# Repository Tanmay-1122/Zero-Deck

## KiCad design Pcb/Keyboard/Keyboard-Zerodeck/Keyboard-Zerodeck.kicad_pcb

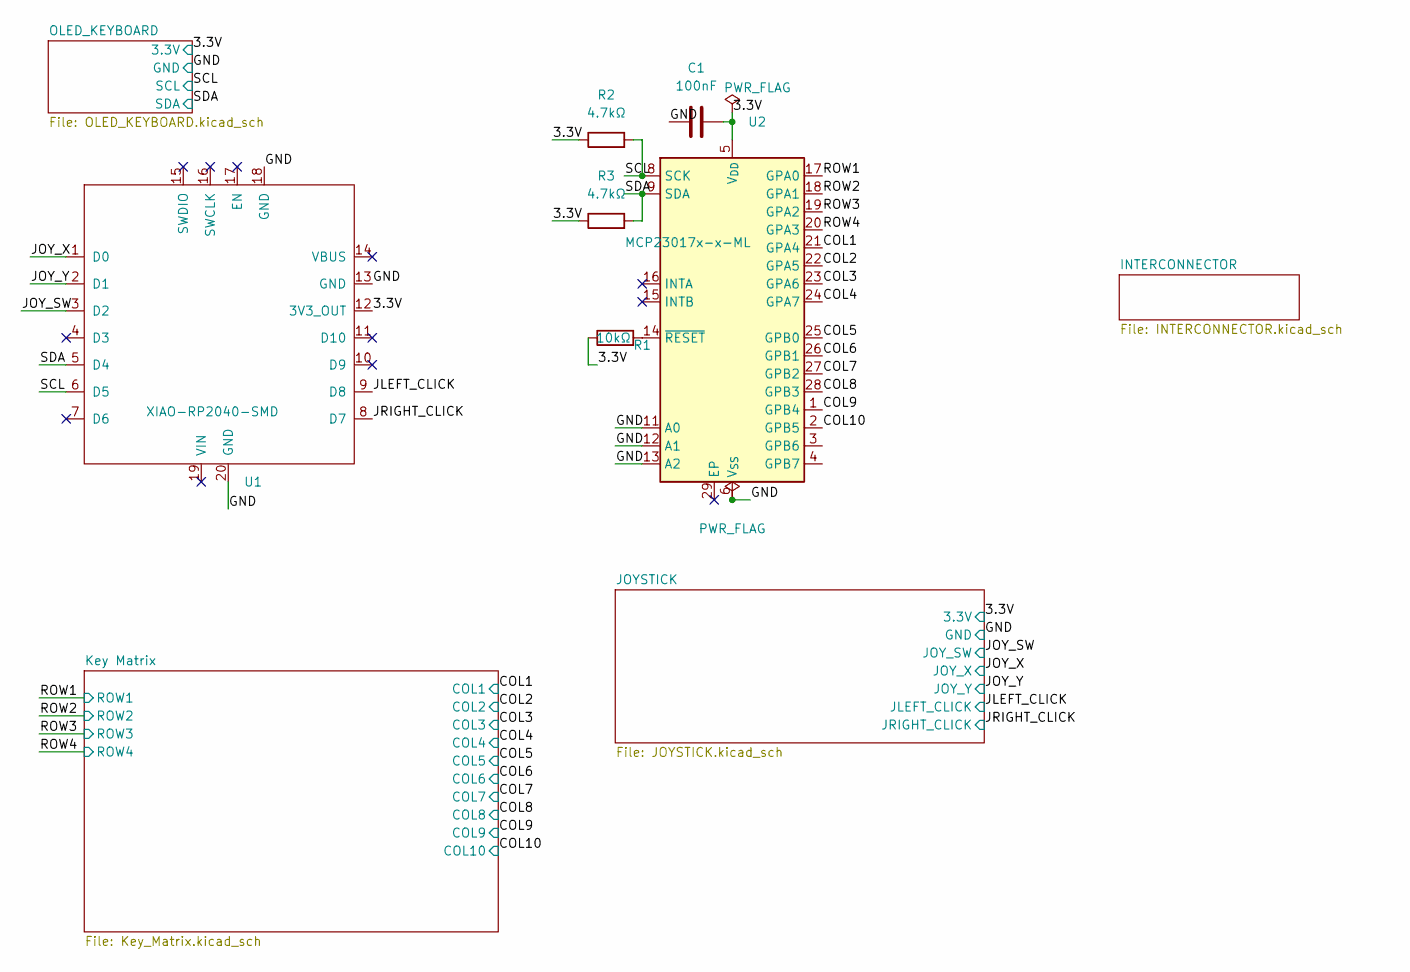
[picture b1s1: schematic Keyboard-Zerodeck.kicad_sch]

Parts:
C1: 100nF; C_0805_2012Metric
R1: 10kΩ; R_0805_2012Metric
R2, R3: 4.7kΩ; R_0805_2012Metric
U1: XIAO-RP2040-SMD
U2: MCP23017x-x-ML; QFN-28-1EP_6x6mm_P0.65mm_EP4.25x4.25mm

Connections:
/3.3V: C1.2, R1.1, R2.1, R3.1, U1.12 (3V3_OUT), U2.5 (V_{DD}); also elsewhere on the board
/COL1: U2.21 (GPA4); also elsewhere on the board
/COL2: U2.22 (GPA5); also elsewhere on the board
/COL3: U2.23 (GPA6); also elsewhere on the board
/COL4: U2.24 (GPA7); also elsewhere on the board
/COL5: U2.25 (GPB0); also elsewhere on the board
/COL6: U2.26 (GPB1); also elsewhere on the board
/COL7: U2.27 (GPB2); also elsewhere on the board
/COL8: U2.28 (GPB3); also elsewhere on the board
/COL9: U2.1 (GPB4); also elsewhere on the board
/COL10: U2.2 (GPB5); also elsewhere on the board
/GND: C1.1, U1.13 (GND), U1.18 (GND), U1.20 (GND), U2.6 (V_{SS}), U2.11 (A0), U2.12 (A1), U2.13 (A2); also elsewhere on the board
/JLEFT_CLICK: U2.3 (GPB6); also elsewhere on the board
/JOY_SW: U1.3 (D2); also elsewhere on the board
/JOY_X: U1.1 (D0); also elsewhere on the board
/JOY_Y: U1.2 (D1); also elsewhere on the board
/JRIGHT_CLICK: U2.4 (GPB7); also elsewhere on the board
/ROW1: U2.17 (GPA0); also elsewhere on the board
/ROW2: U2.18 (GPA1); also elsewhere on the board
/ROW3: U2.19 (GPA2); also elsewhere on the board
/ROW4: U2.20 (GPA3); also elsewhere on the board
/SCL: R2.2, U1.6 (D5), U2.8 (SCK)
/sda: R3.2, U1.5 (D4), U2.9 (SDA)
unnamed: R1.2, U2.14 (~RESET)

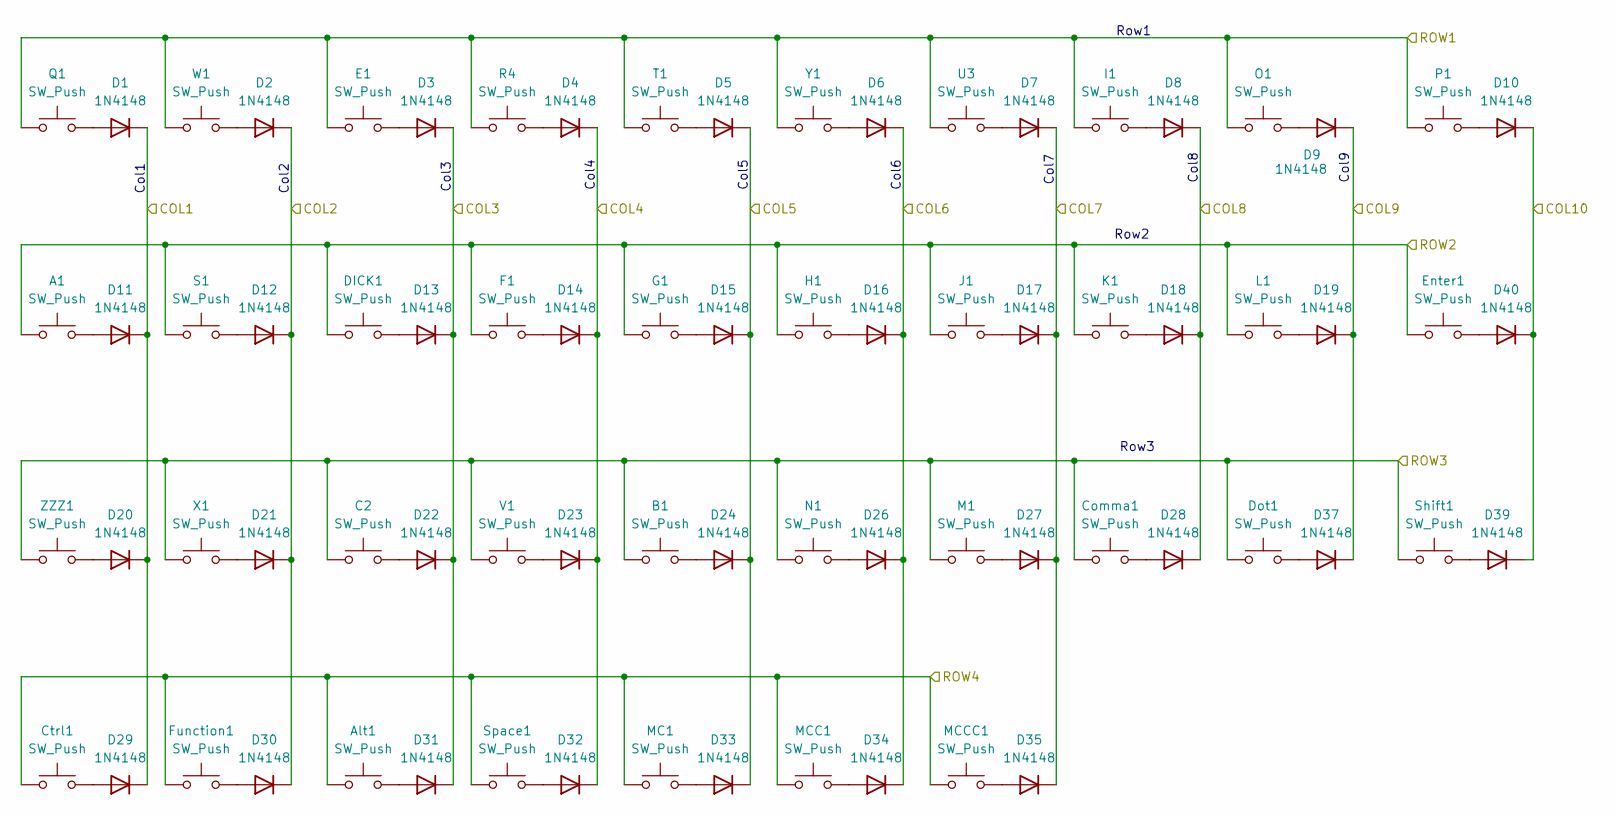
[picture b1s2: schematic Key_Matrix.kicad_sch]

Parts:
A1: SW_Push; Kailh_socket_PG1350
Alt1: SW_Push; Kailh_socket_PG1350
B1: SW_Push; Kailh_socket_PG1350
C2: SW_Push; Kailh_socket_PG1350
Comma1: SW_Push; Kailh_socket_PG1350
Ctrl1: SW_Push; Kailh_socket_PG1350
D1, D2, D3, D4, D5, D6, D7, D8, D9, D10, D11, D12, D13, D14, D15, D16, D17, D18, D19, D20, D21, D22, D23, D24, D26, D27, D28, D29, D30, D31, D32, D33, D34, D35, D37, D39, D40: 1N4148; D_SOD-123
DICK1: SW_Push; Kailh_socket_PG1350
Dot1: SW_Push; Kailh_socket_PG1350
E1: SW_Push; Kailh_socket_PG1350
Enter1: SW_Push; Kailh_socket_PG1350
F1: SW_Push; Kailh_socket_PG1350
Function1: SW_Push; Kailh_socket_PG1350
G1: SW_Push; Kailh_socket_PG1350
H1: SW_Push; Kailh_socket_PG1350
I1: SW_Push; Kailh_socket_PG1350
J1: SW_Push; Kailh_socket_PG1350
K1: SW_Push; Kailh_socket_PG1350
L1: SW_Push; Kailh_socket_PG1350
M1: SW_Push; Kailh_socket_PG1350
MC1: SW_Push; Kailh_socket_PG1350
MCC1: SW_Push; Kailh_socket_PG1350
MCCC1: SW_Push; Kailh_socket_PG1350
N1: SW_Push; Kailh_socket_PG1350
O1: SW_Push; Kailh_socket_PG1350
P1: SW_Push; Kailh_socket_PG1350
Q1: SW_Push; Kailh_socket_PG1350
R4: SW_Push; Kailh_socket_PG1350
S1: SW_Push; Kailh_socket_PG1350
Shift1: SW_Push; Kailh_socket_PG1350
Space1: SW_Push; Kailh_socket_PG1350
T1: SW_Push; Kailh_socket_PG1350
U3: SW_Push; Kailh_socket_PG1350
V1: SW_Push; Kailh_socket_PG1350
W1: SW_Push; Kailh_socket_PG1350
X1: SW_Push; Kailh_socket_PG1350
Y1: SW_Push; Kailh_socket_PG1350
ZZZ1: SW_Push; Kailh_socket_PG1350

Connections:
/COL1: D1.1 (K), D11.1 (K), D20.1 (K), D29.1 (K); also elsewhere on the board
/COL2: D2.1 (K), D12.1 (K), D21.1 (K), D30.1 (K); also elsewhere on the board
/COL3: D3.1 (K), D13.1 (K), D22.1 (K), D31.1 (K); also elsewhere on the board
/COL4: D4.1 (K), D14.1 (K), D23.1 (K), D32.1 (K); also elsewhere on the board
/COL5: D5.1 (K), D15.1 (K), D24.1 (K), D33.1 (K); also elsewhere on the board
/COL6: D6.1 (K), D16.1 (K), D26.1 (K), D34.1 (K); also elsewhere on the board
/COL7: D7.1 (K), D17.1 (K), D27.1 (K), D35.1 (K); also elsewhere on the board
/COL8: D8.1 (K), D18.1 (K), D28.1 (K); also elsewhere on the board
/COL9: D9.1 (K), D19.1 (K), D37.1 (K); also elsewhere on the board
/COL10: D10.1 (K), D39.1 (K), D40.1 (K); also elsewhere on the board
/ROW1: E1.1, I1.1, O1.1, P1.1, Q1.1, R4.1, T1.1, U3.1, W1.1, Y1.1; also elsewhere on the board
/ROW2: A1.1, DICK1.1, Enter1.1, F1.1, G1.1, H1.1, J1.1, K1.1, L1.1, S1.1; also elsewhere on the board
/ROW3: B1.1, C2.1, Comma1.1, Dot1.1, M1.1, N1.1, Shift1.1, V1.1, X1.1, ZZZ1.1; also elsewhere on the board
/ROW4: Alt1.1, Ctrl1.1, Function1.1, MC1.1, MCC1.1, MCCC1.1, Space1.1; also elsewhere on the board
unnamed: D1.2 (A), Q1.2
unnamed: D2.2 (A), W1.2
unnamed: D3.2 (A), E1.2
unnamed: D4.2 (A), R4.2
unnamed: D5.2 (A), T1.2
unnamed: D6.2 (A), Y1.2
unnamed: D7.2 (A), U3.2
unnamed: D8.2 (A), I1.2
unnamed: D9.2 (A), O1.2
unnamed: D10.2 (A), P1.2
unnamed: A1.2, D11.2 (A)
unnamed: D12.2 (A), S1.2
unnamed: D13.2 (A), DICK1.2
unnamed: D14.2 (A), F1.2
unnamed: D15.2 (A), G1.2
unnamed: D16.2 (A), H1.2
unnamed: D17.2 (A), J1.2
unnamed: D18.2 (A), K1.2
unnamed: D19.2 (A), L1.2
unnamed: D20.2 (A), ZZZ1.2
unnamed: D21.2 (A), X1.2
unnamed: C2.2, D22.2 (A)
unnamed: D23.2 (A), V1.2
unnamed: B1.2, D24.2 (A)
unnamed: D26.2 (A), N1.2
unnamed: D27.2 (A), M1.2
unnamed: Comma1.2, D28.2 (A)
unnamed: Ctrl1.2, D29.2 (A)
unnamed: D30.2 (A), Function1.2
unnamed: Alt1.2, D31.2 (A)
unnamed: D32.2 (A), Space1.2
unnamed: D33.2 (A), MC1.2
unnamed: D34.2 (A), MCC1.2
unnamed: D35.2 (A), MCCC1.2
unnamed: D37.2 (A), Dot1.2
unnamed: D39.2 (A), Shift1.2
unnamed: D40.2 (A), Enter1.2

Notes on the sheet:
Col2
Col4
Col7
Col8
Row2
Col3
Row1
Col1
Col5
Col9
Row3
Col6

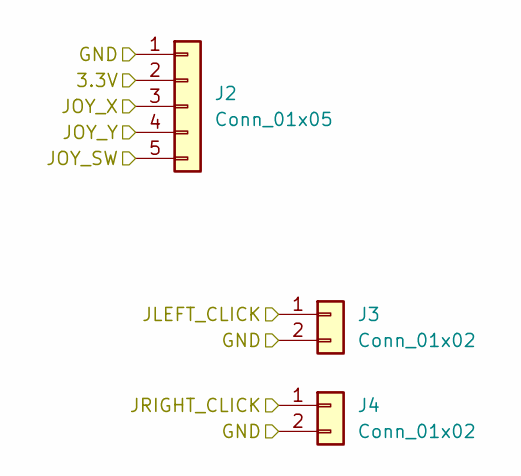
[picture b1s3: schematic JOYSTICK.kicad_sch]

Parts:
J2: Conn_01x05; JST_PH_S5B-PH-K_1x05_P2.00mm_Horizontal
J3, J4: Conn_01x02; JST_PH_S2B-PH-K_1x02_P2.00mm_Horizontal

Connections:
/3.3V: J2.2; also elsewhere on the board
/GND: J2.1, J3.2, J4.2; also elsewhere on the board
/JLEFT_CLICK: J3.1; also elsewhere on the board
/JOY_SW: J2.5; also elsewhere on the board
/JOY_X: J2.3; also elsewhere on the board
/JOY_Y: J2.4; also elsewhere on the board
/JRIGHT_CLICK: J4.1; also elsewhere on the board

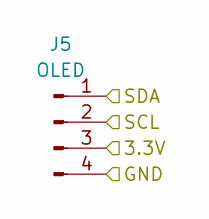
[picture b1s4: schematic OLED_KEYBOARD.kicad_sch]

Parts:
J5: OLED

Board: 2 copper layers, 83 parts (3 on the bottom side), 61 nets, no tracks yet.
